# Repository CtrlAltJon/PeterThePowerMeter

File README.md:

# ⚡ Peter The Power Meter
### with ESP8266 and ADS1115

<p align="center">
  
</p>

## ⚠️ Disclaimer

> [!CAUTION]
> ### ⚠️ IMPORTANT SAFETY WARNING & DISCLAIMER
> **THIS PROJECT INVOLVES WORKING WITH HIGH VOLTAGE (230VAC). HIGH VOLTAGE CAN CAUSE SEVERE INJURY, ELECTROCUTION, OR DEATH. FIRE HAZARD IS ALSO PRESENT.**
>
> This project is provided "as is", for educational and hobbyist purposes only. By using any part of this project (including hardware designs, PCB layouts, and software), you acknowledge and agree to the following:
>
> * **Assumption of Risk:** You are solely responsible for your own safety and for any damage caused by the assembly, testing, or use of this device.
> * **No Liability:** The author(s) shall not be held liable for any direct or indirect damages, including but not limited to: hardware failure, data loss, property damage (fire, short circuits), personal injury, or death, resulting from the use or misuse of this project.
> * **Assembly & Modification:** Any errors in assembly, soldering (e.g., solder bridges), component selection, firmware modification or others actions are the sole responsibility of the user.
> * **No Warranty:** There is no guarantee regarding the accuracy of measurements, the stability of the software, or the safety of the hardware design for long-term use.
> * **Local Standards:** It is the user's responsibility to ensure that the device complies with local electrical codes and safety regulations.
>
> **IF YOU ARE NOT EXPERIENCED IN WORKING WITH MAINS VOLTAGE, DO NOT ATTEMPT TO BUILD THIS PROJECT.**

## 📜 Revision History
* **00:** First release (30/05/2026)
* **01:** Hardware optimizations and professional safety compliance updates (17/06/2026)
  * **Complete 2.5mm High-Voltage Isolation:** Optimized the High Voltage (HV) layout to strictly enforce a minimum 2.5mm track-to-track clearance across the entire mains section. This includes adding physical PCB isolation slots (milling) between R28, R29, F1, and J3 (pin 2), and shifting transformer TR1 along with adjacent resistors slightly upward to eliminate any tight spacings.
  * **Industrial-Grade Reinforced Insulation:** Preserved the robust **8.0mm isolation barrier** natively designed between the HV and Low Voltage (LV) domains. By combining this wide clearance with the new track-to-track optimizations, the board fully satisfies the strict **Reinforced Insulation** requirements of the **IEC/EN 62368-1** standard (aligning with household and industrial appliance safety regulations like IEC 60335-1 / IEC 60730-1), drastically setting this architecture apart from typical, uncertified DIY designs.
  * **Power Rail & Logic Level Optimization:** Removed 1 pin from connector J11 to eliminate the +5VDC routing to the lateral pcb, successfully migrating the CH340C USB-to-Serial subsystem entirely to a +3.3VDC power rail.
  * **Component Reconfiguration:** Rewired pin 4 (V3) of the CH340C directly to the +3.3VDC rail (mandatory for stable 3.3V operation) while retaining C9 in the layout to act as an active power supply decoupling filter instead of a standard bypass to GND.

## 💡 Design Rationale & Project Overview

### 1.1 System Architecture
This project is a Digital Power Meter designed for real-time energy monitoring with acoustic alarm when a threshold is exceeded. The system is engineered to fit within a standard 1-module DIN rail enclosure (roughly the size of a standard miniature circuit breaker), making it ideal for integration into domestic electrical panels.

*Note: At the moment, the 3D design/CAD file for the DIN enclosure is not available. Contributions regarding the design of a suitable enclosure are highly welcome and would be a valuable addition to this project.*

The system architecture is based on the ESP8266 (ESP-12F) microcontroller, leveraging its Wi-Fi capabilities for IoT integration and an ADS1115 to read voltage and current. For system health, an onboard TFPT1206L1002DV temperature sensor is included to monitor the internal thermal conditions of the enclosure.

For local interaction, the device features a 0.96" color LCD display that provides real-time data visualization and configuration menus. Users can navigate through multiple data pages and perform basic setup tasks using a multi-function physical button. Additionally, the system hosts a built-in Web Server, allowing for advanced remote configuration, firmware updates (OTA), and detailed system management via an intuitive Web UI.

The measurement stage utilizes two primary sensors:
* **Voltage Sensing:** Handled via a dedicated voltage transformer ZMPT107-1 (TR1) for galvanic isolation and safety.
* **Current Sensing:** Implemented using the SCT-013 split-core current transformer (clamp meter).

Both sensors provide a 1VAC sinusoidal output. These signals are conditioned via a voltage divider network and sampled by an ADS1115 16-bit ADC, which communicates with the MCU via the I2C protocol.

### 1.2 Hardware Features & User Interface

<p align="center">
  
</p>

To optimize GPIO usage, a PCF8574 I/O expander is employed for digital signal management and future use. The user interface consists of:
* **Buttons:** A multi-function navigation button (Short press: Page toggle | Long press: Confirm/Action) and a dedicated Pin-hole Hardware Reset button connected directly to Pin 1 (RST) of the ESP8266.
* **Acoustic Feedback:** An active piezoelectric buzzer triggers an audible alarm when a software-defined power threshold is exceeded.
* **Thermal Monitoring:** An onboard TFPT1206L1002DV temperature sensor (PTC thermistor) is integrated into the circuit. This component allows the system to monitor the internal temperature of the enclosure.
* **Display:** A 0.96" Color LCD for local monitoring and basic interaction.
* **Web Server:** A Web User Interface for remote monitoring and full system configuration.

### 1.3 Power Supply & Protection
The device supports 2 power input options and 1 input 230VAC for Voltage reading:

* **Terminal Block (J1):** Accepts a +5VDC regulated supply.

> [!CAUTION]
> **No reverse polarity protection:** This input currently lacks reverse polarity protection; correct orientation is mandatory.

<p align="center">
  
</p>

* **USB Connector (J2):** For secondary power or debugging.
    * *Communication & Debugging:* This interface utilizes a CH340C USB-to-Serial bridge and a UMH3NFHATN transistor pair to communicate with the ESP8266. This setup enables full debugging, serial communication, and firmware programming (automatic reset/bootloader entry).
    * *Safety Feature:* The board implements a dual Schottky diode protection circuit on the positive rails of both J1 and J2. This prevents back-feeding, though it is recommended to disconnect J1 when using USB power.
    * *Overcurrent Protection:* The +5VDC main rail is protected by a MF-NSMF050-2 PTC (Resettable Fuse) rated at 500mA.
* **AC Voltage Input (J3):** High-voltage input for the ZMPT107-1 transformer.
    * *Polarity Recommendation:* Although the transformer operates on AC, it is strictly recommended to respect the Phase (L) and Neutral (N) markings.
    <p align="center">
      
    </p>

    * *Safety Rationale:* The protection fuse is located exclusively on the Phase line. Inverting the polarity would mean that, in the event of a fault or a blown fuse, the Neutral line would be disconnected while the entire internal circuit remains energized (live) through the Phase line. This creates a severe electrocution hazard even when the device appears to be non-functional.
    * *Safety Design:* The circuit features a 250mA T (Slow-blow) fuse placed exclusively on the Phase line. Additionally, the line is equipped with three resistors in series designed to limit the current to 1mA RMS at 230V, providing an essential layer of protection for the sensing stage.

### 1.4 Operational Limits & Grid Compatibility
This device is specifically designed and calibrated for 230VAC/50Hz Phase-Neutral grids (Standard European Grid).

* **Voltage Specificity:** The internal components, including the protection resistors and the ZMPT107-1 transformer ratio, are optimized for 230V. Use with different mains voltages (e.g., 110-120V) may result in inaccurate readings or insufficient signal-to-noise ratio.
* **Frequency Specificity:** The system is tuned for 50Hz operation. While the magnetic components (TR1 and CT) can physically handle 60Hz, the firmware's sampling window and RMS calculation algorithms are optimized for a 20ms period.
* **Warning:** Operation on different grid standards, high-voltage industrial lines, or Phase-to-Phase configurations (without a neutral line) may exceed the safety ratings of the components and the fuse, leading to hardware failure or fire hazard.

## 🌐 2.0 Connectivity & Software Integration
The firmware architecture features a built-in Web Server for real-time monitoring, local configuration, and connections management (Wi-Fi and MQTT). The device natively supports the MQTT protocol for a smart home integration with platforms such as Home Assistant.

### 2.0.1 LCD User Interface (Vertical Orientation)
Navigation is handled via the multi-function button (Short press: Page toggle | Long press: Confirm/Action).

* **Page 1: Real-time Monitor**
    * Power: Current power consumption displayed in kW.
    * Temperature: PCB temperature in °C.
    * Graph: A rolling history graph showing power trends (approx. 1-minute window).
    * Status Badges: Dynamic icons for Wi-Fi connection status and MQTT connection status.
* **Page 2: Power Threshold Configuration**
    * Displays the active alarm threshold (Watts).
    * Allows cyclic adjustment of the new threshold (100W increments) via long-press.
* **Page 3: Voltage Monitoring**
    * Displays the real-time mains voltage (V).
* **Page 4: Acoustic Alarm Settings**
    * Displays and cycles through buzzer modes: Continuous, Slow Intermittent, or Fast Intermittent.
* **Page 5: Save Settings**
    * Summarizes settings. Action: A long-press commits settings to non-volatile memory.
* **Page 6: System Information**
    * Displays network details: Hostname, SSID, IP Address, and Firmware Version.
* **Page 7: System Tools**
    * AP Mode, Reboot device, and Reset (Factory Reset). Requires a long-press with a visual timer-bar.

### 2.0.2 Web Interface & Configuration
The device features a responsive Web UI. Users can connect via browser to the device's IP (visible on LCD page 6).

#### Home Page (Real-Time Dashboard)
* **Connectivity Status:** Dynamic badges for AP Mode, Wi-Fi, and MQTT.
* **Live Telemetry:** Power (W), Voltage (V), Current (A).
* **System Uptime:** Tracks operational time in "Days hh:mm:ss" format.
* **Data Refresh:** Auto-refresh every 10 seconds or manual button.

#### Configuration Page
* **General Settings:** Hostname, Manufacturer, Language (IT/EN), Alarm Threshold, Buzzer Mode.
* **Wi-Fi Setup:** Credentials and IP Assignment (DHCP or Static IP).
* **MQTT Setup (Optional):** Broker IP, Port, and Authentication.
* **Buttons:** Save & Reboot, Reboot, Firmware Update (OTA), Home.

## 🛠️ Manufacturing & Assembly Notes

### 3.0 Hardware Configuration
**ADS1115 I2C Address Selection:** Hardware-defined through two "0-Ohm bridge" resistors: R16 and R17. Only one of these resistors must be populated at a time:
* **R16:** Connects the ADDR pin to +3.3V, ADS1115 Address `0x49`
* **R17:** Connects the ADDR pin to GND, ADS1115 Address `0x48` (Default).

**Safety Design:** To prevent assembly errors, the PCB layout utilizes a shared common pad for both R16 and R17. This physical constraint makes it nearly impossible to populate both resistors simultaneously, effectively protecting the +3.3V rail from a direct short circuit to Ground. However, be careful when assembling.

## Assembly Layout: TOP Layer
<p align="center">
  
</p>

## Assembly Layout: BOTTOM Layer
<p align="center">
  
</p>

## Dimensions
<p align="center">
  
</p>

## 💻 4.0 Firmware
Peter The Power Meter has an embedded firmware designed for real-time single-phase energy monitoring. The system samples AC voltage and current waveforms, calculates Root Mean Square (RMS) values and active power consumption, provides a multi-page visual interface on a TFT display, and integrates with home automation systems via the MQTT protocol.

### Technical Specifications
* **Language:** C++ (Standard C++11/14).
* **Framework:** Arduino Core for ESP8266.
* **Development Environment:** PlatformIO.
* **Core Hardware:** Espressif ESP8266 (e.g., Wemos D1 Mini).
* **Data Acquisition:** External ADS1115 16-bit ADC connected via I2C for high-precision differential sampling.
* **Sensor Support:** Current Transformers (SCT-013), Voltage Transformers (ZMPT107-1), and PTC temperature sensors (TFPT1206).

### Key Features
* **High-Speed Sampling & RMS Calculation:** Performs rapid sampling of sinusoidal signals to calculate precise Voltage RMS, Current RMS, and Active Power (W) over a sliding 1-second window.
* **Display Management:** Features a multi-page User Interface on an ST7735 (0.96" TFT) display; includes real-time power trend graphs, connectivity status badges, and system information pages.
* **IoT & Home Automation:**
    * **MQTT Telemetry:** Transmits energy data using a time-weighted average calculated over the publishing interval (default 20s).
    * **Home Assistant Integration:** Fully supports Auto-Discovery, automatically creating sensors and configuration entities (Select/Number) within Home Assistant.
* **Embedded Web Server:** A built-in web portal protected by HTTP Basic Authentication allows users to configure WiFi credentials, MQTT settings, alarm thresholds, and perform fine sensor calibration (offset and scale).
* **Alarm System:** Manages a buzzer via a PCF8574 I/O expander with programmable modes (Continuous, Slow Pulse, Fast Pulse) triggered when power exceeds a user-defined threshold.
* **Reliability & Maintenance:**
    * **Resilient Connectivity:** Implements an exponential backoff strategy for WiFi and MQTT reconnection.
    * **OTA Updates:** Supports Over-The-Air firmware updates through the web interface.
    * **Localization:** Built-in multi-language support (English and Italian) using PROGMEM to optimize RAM usage.

### 4.0.1 Sensor Calibration & Physics Guide (include/config.h)
The following constants define how the raw electrical signals from the sensors are translated into human-readable values (Amps, Volts, Watts).

#### Current Conversion (FACTOR_A_V)
* **Description:** This is the scaling factor for the Current Transformer (CT). It converts the voltage measured by the ADC into RMS Amperes.
* **Formula:** `I_RMS = V_ADC * FACTOR_A_V`.
* **Configuration:** The `FACTOR_A_V` of 25.0f is set based on the characteristics of the SCT-013 current transformer.
* **When to change:**
    1. You replace the SCT-013 with a model that has a different Current/Voltage ratio (e.g., 30A/1V or 100A/50mA).
    2. You add or change an external burden resistor in parallel with the CT output.

#### Voltage Conversion (FACTOR_V_V)
* **Description:** This factor scales the low-voltage signal from the ZMPT107-1 transformer back to the actual grid voltage.
* **Formula:** `V_Grid = V_ADC * FACTOR_V_V`.
* **Configuration:** The `FACTOR_V_V` of 246.0f is derived directly from the ratio of the primary resistance (246KΩ) to the burden resistance (1KΩ).
* **When to change:** If you modify the scaling "divider" (e.g., changing series resistors on the Primary side or the burden resistor on the Secondary side).

#### ADC Precision & Sampling Rate
* **ADC Precision:** `ADS_GAIN` (GAIN_TWO) sets the full-scale range to ±2.048V, with an `ADS_MULTIPLIER` of 0.0000625.
* **Sampling Rate:** 860 Samples Per Second is the maximum stable rate for the ADS1115 and provides high fidelity for power calculations.

#### Noise, Safety, and Temperature
* **CURRENT_NOISE_FLOOR (0.002f):** A software filter that forces the current to 0.0A if the measured voltage is below 2mV.
* **VOLTAGE_MIN_THRESHOLD (50.0f):** If the measured voltage is below 50V, the system assumes the sensor is faulty and falls back to 230V.
* **Temperature Monitoring:** The firmware averages 10 readings (`PTC_AVG_SAMPLES`) to stabilize the PTC sensor data; if the temperature exceeds `TEMP_WARNING_THRESHOLD` (45.0°C), the display text turns RED.

| Constant | Default Value | Unit | Description |
| :--- | :--- | :--- | :--- |
| FACTOR_A_V | 25.0 | A/V | Ratio of Amps per Volt from the CT circuit. |
| FACTOR_V_V | 246.0 | V/V | Ratio of Grid Volts per Volt from the VT circuit. |
| ADS_GAIN | GAIN_TWO | - | Sets ADC input range to ±2.048V. |
| ADS_SPS | 860 | Hz | Samples taken per second from the AC wave. |
| CURRENT_NOISE_FLOOR | 0.002 | V | Minimum voltage to consider a valid current reading. |
| VOLTAGE_MIN_THRESHOLD | 50.0 | V | Voltage below which the system uses a fallback value. |

### 4.0.2 Per-device calibration limits (include/config.h)
These constants define the acceptable range and default values for the calibration parameters stored in EEPROM.

* **Scale Factors:** `CAL_SCALE_DEFAULT` is 1.0f (no correction), with a range between 0.1f and 10.0f.
* **Voltage Offset Limits:** -500.0f to 500.0f Volts.
* **Current Offset Limits:** -100.0f to 100.0f Amperes.
* **Temperature Offset Limits:** -50.0f to 50.0f degrees Celsius.

| Constant | Default/Range | Unit | Description |
| :--- | :--- | :--- | :--- |
| CAL_SCALE_DEFAULT | 1.0f | - | Default multiplicative scale factor. |
| CAL_SCALE_MIN | 0.1f | - | Minimum allowed value for scale factors. |
| CAL_SCALE_MAX | 10.0f | - | Maximum allowed value for scale factors. |
| CAL_OFFSET_V_MIN | -500.0f | V | Minimum allowed voltage offset. |
| CAL_OFFSET_V_MAX | 500.0f | V | Maximum allowed voltage offset. |
| CAL_OFFSET_A_MIN | -100.0f | A | Minimum allowed current offset. |
| CAL_OFFSET_A_MAX | 100.0f | A | Maximum allowed current offset. |
| CAL_OFFSET_TEMP_MIN | -50.0f | °C | Minimum allowed temperature offset. |
| CAL_OFFSET_TEMP_MAX | 50.0f | °C | Maximum allowed temperature offset. |

### 4.0.3 PTC Calibration & Hardware (include/config.h)
The device monitors internal temperature using the TFPT1206 series PTC sensor.

* **PTC_V_SOURCE:** 3.3f (Standard logic voltage).
* **PTC_R_PULLUP:** 33,000 Ω (Fixed resistor R7).
* **ADC Compensation:** Constants `PTC_R_DIVIDER_TOTAL` and `PTC_R_DIVIDER_LOAD` compensate for the voltage divider on the ESP8266 ADC input stage.
* **Sensor Characteristics:** `PTC_NOMINAL_RES` (10,000 Ω at 25°C) and `PTC_COEFF` (0.00411) define the resistance-to-temperature curve.

| Constant | Default Value | Unit | Description |
| :--- | :--- | :--- | :--- |
| PTC_V_SOURCE | 3.3 | V | Logic source voltage for the sensing branch. |
| PTC_R_PULLUP | 33,000 | Ω | Fixed pull-up resistor ($R_7$) in the divider. |
| PTC_NOMINAL_RES | 10,000 | Ω | PTC resistance at 25°C. |
| PTC_COEFF | 0.00411 | - | TCR (Temperature Coefficient) of the sensor. |
| PTC_R_DIVIDER_TOTAL | 100,220 | Ω | ADC input stage total resistance ($R_{21} + R_{22}$). |

## 🤝 Contributing

Contributions, issues, and feature requests are welcome!
Feel free to [open an issue](https://github.com/CtrlAltJon/PeterThePowerMeter/issues) or submit a pull request.

## 🔜 Coming Soon
I am currently in the process of refining and cleaning up the firmware comments to ensure the code is as clear and readable as possible, even though the project is fully functional.
I am also polishing the documentation and preparing additional guides that I'll upload to the repository soon.
Currently seeking help with:
* Enclosure Design: I'm looking for contributors to design a 3D-printable enclosure compatible with a standard 1-module DIN rail format. I think I'll be able to upload at least the STL file soon, but not the project.

## 📝 License

This project is licensed under the MIT License. See the [LICENSE](LICENSE) file for details.

## 👤 Author

CtrlAltJon

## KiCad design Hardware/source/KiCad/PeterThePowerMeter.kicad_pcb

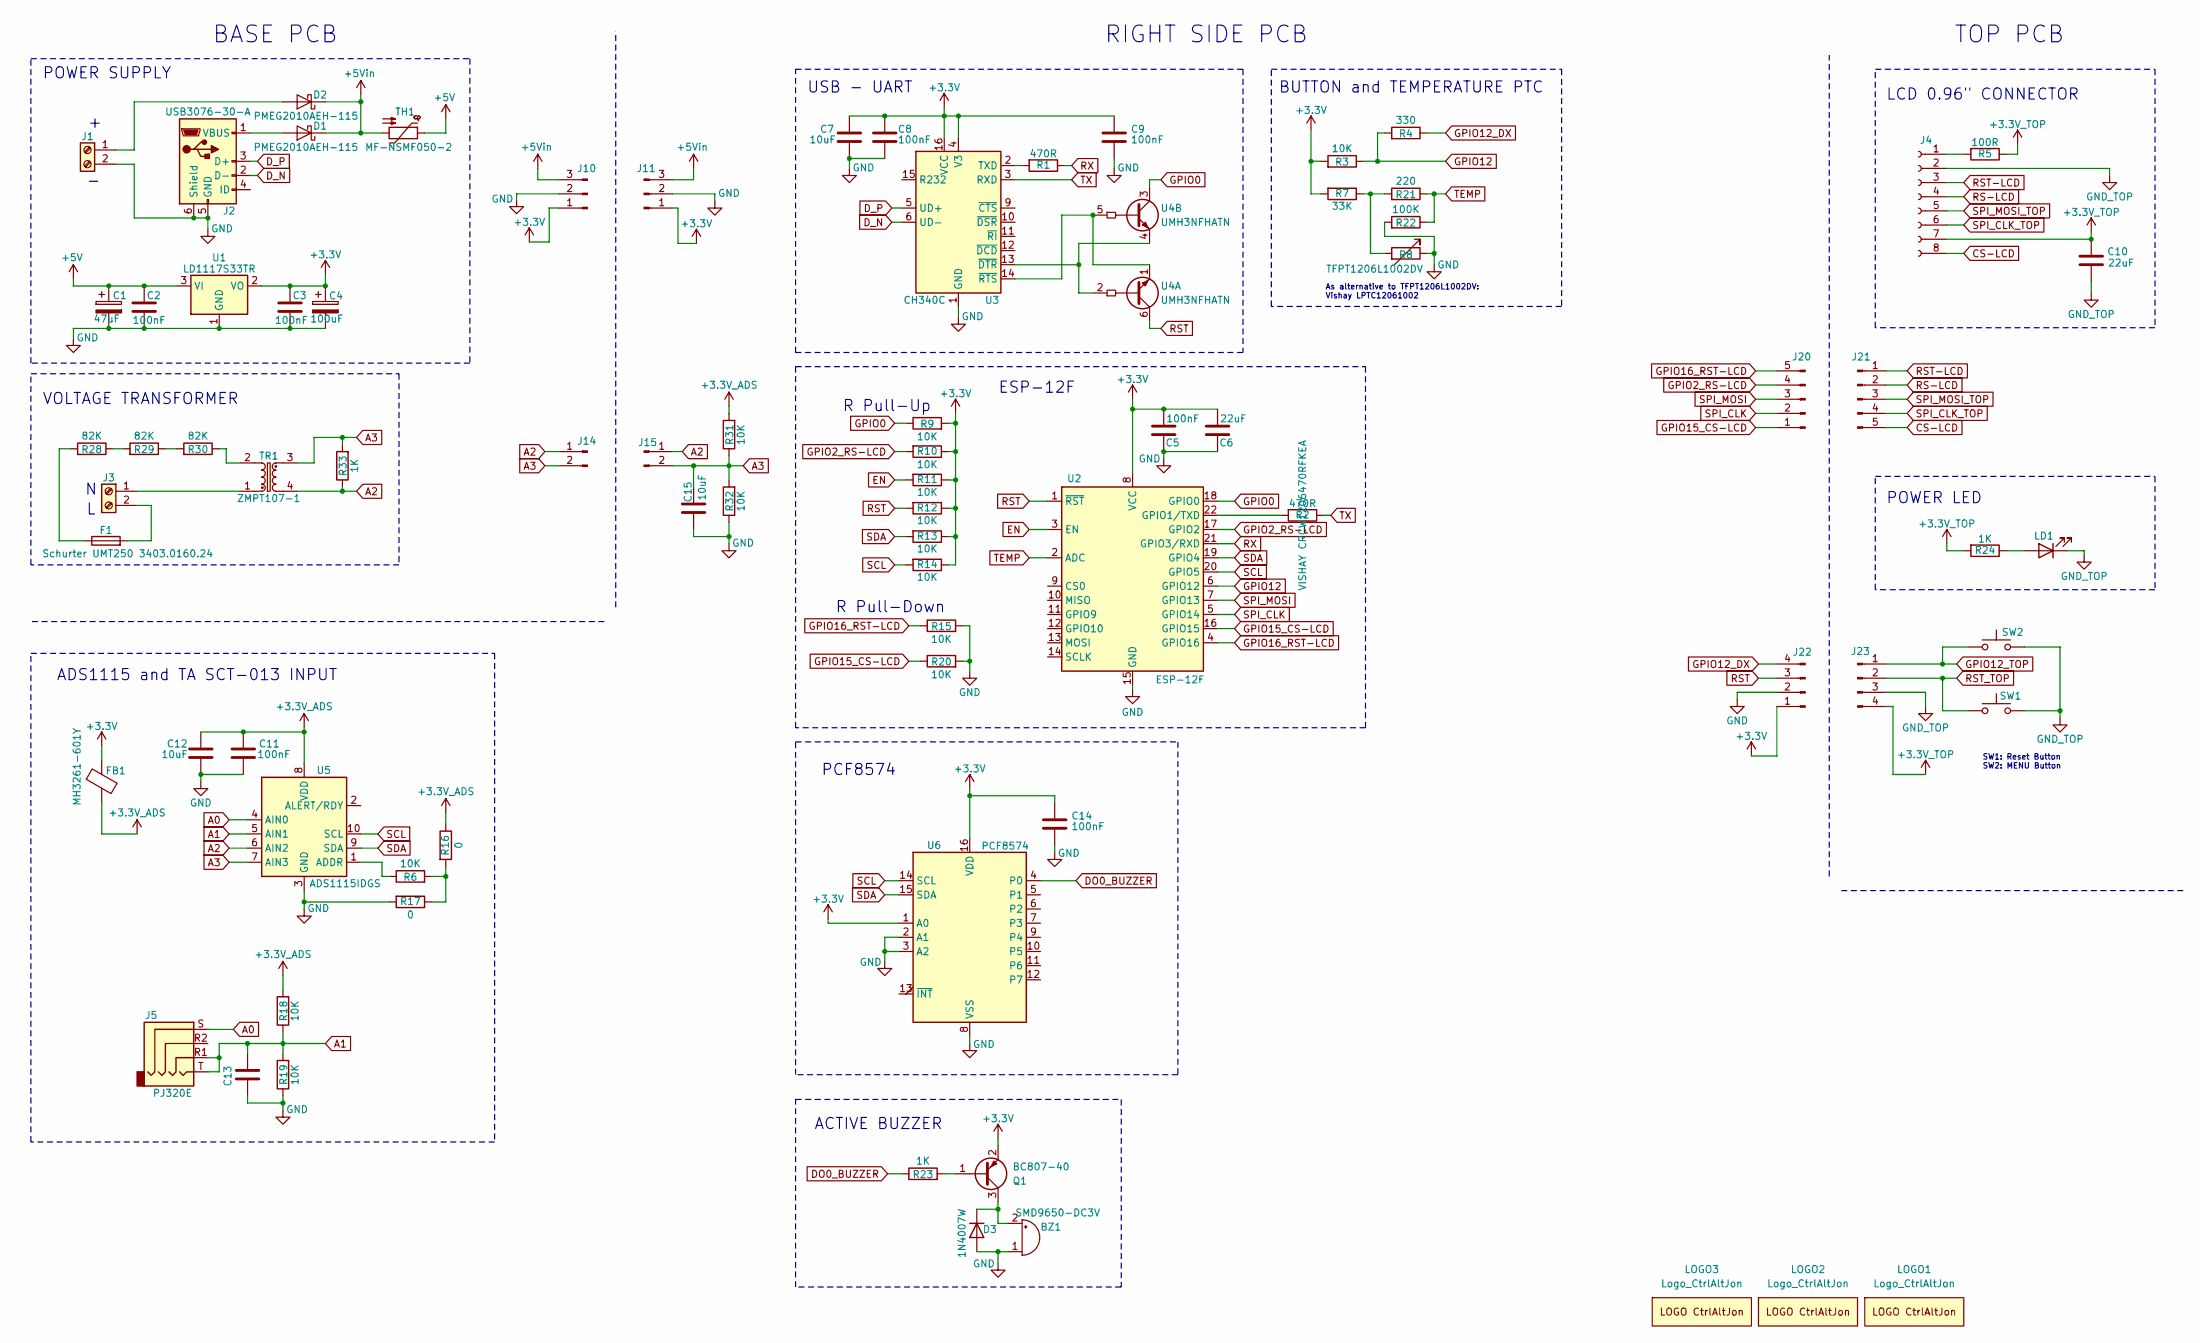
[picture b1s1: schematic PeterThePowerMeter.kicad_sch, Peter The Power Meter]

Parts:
BZ1: SMD9650-DC3V; Buzzer_CUI_CPT-9019S-SMT; LCSC C49246960
C1: 47uF; CP_Radial_D6.3mm_P2.50mm; LCSC C1580807
C2, C3, C5, C8, C9, C11, C14: 100nF; C_1206_3216Metric_Pad1.33x1.80mm_HandSolder; LCSC C2167356
C4: 100uF; CP_Radial_D6.3mm_P2.50mm; LCSC C1589590
C6, C10: 22uF; C_1206_3216Metric_Pad1.33x1.80mm_HandSolder; LCSC C318754
C7, C12, C13, C15: 10uF; C_1206_3216Metric_Pad1.33x1.80mm_HandSolder; LCSC C89632
D1, D2: PMEG2010AEH-115; D_SOD-123F; LCSC C110921
D3: 1N4007W; D_SOD-123; LCSC C3018540
F1: Schurter UMT250 3403.0160.24; Fuse_Schurter_UMZ250; LCSC C3163460
FB1: MH3261-601Y; L_1206_3216Metric; LCSC C840591
J1, J3: Screw_Terminal_01x02; PhoenixContact_MSTBA_2,5_2-G_1x02_P5.00mm_Horizontal; LCSC C90074
J2: USB3076-30-A; USB_Micro-B_GCT_USB3076-30-A; LCSC C6007475
J4: Conn_01x08_Socket; Hirose_FH12-8S-0.5SH_1x08-1MP_P0.50mm_Horizontal
J5: PJ320E; Jack_3.5mm_PJ320E_Horizontal; LCSC C2939183
J10: Conn_01x03_Pin; PinHeader_1x03_P2.54mm_Vertical
J11: Conn_01x03_Pin; PinHeader_1x03_P2.54mm_Horizontal
J14: Conn_01x02_Pin; PinHeader_1x02_P2.54mm_Vertical
J15: Conn_01x02_Pin; PinHeader_1x02_P2.54mm_Horizontal
J20: Conn_01x05_Pin; PinHeader_1x05_P2.54mm_Horizontal
J21: Conn_01x05_Pin; PinHeader_1x05_P2.54mm_Vertical
J22: Conn_01x04_Male; PinHeader_1x04_P2.54mm_Horizontal
J23: Conn_01x04_Male; PinHeader_1x04_P2.54mm_Vertical
LD1: LED; LED_1206_3216Metric; LCSC C133134
LOGO1, LOGO2, LOGO3: Logo_CtrlAltJon
Q1: BC807-40; SOT-23; LCSC C5184433
R1, R2: 470R; R_1206_3216Metric_Pad1.30x1.75mm_HandSolder; LCSC C844876
R3, R6, R9, R10, R11, R12, R13, R14, R15, R18, R19, R20, R31, R32: 10K; R_1206_3216Metric_Pad1.30x1.75mm_HandSolder; LCSC C132649
R4: 330; R_1206_3216Metric_Pad1.30x1.75mm_HandSolder; LCSC C114944
R5: 100R; R_1206_3216Metric_Pad1.30x1.75mm_HandSolder; LCSC C137392
R7: 33K; R_1206_3216Metric_Pad1.30x1.75mm_HandSolder; LCSC C7233588
R8: TFPT1206L1002DV; R_1206_3216Metric_Pad1.30x1.75mm_HandSolder; LCSC C2154230
R16, R17: 0; R_1206_3216Metric_Pad1.30x1.75mm_HandSolder; LCSC C137394
R21: 220; R_1206_3216Metric_Pad1.30x1.75mm_HandSolder; LCSC C137353
R22: 100K; R_1206_3216Metric_Pad1.30x1.75mm_HandSolder; LCSC C844863
R23, R24, R33: 1K; R_1206_3216Metric_Pad1.30x1.75mm_HandSolder; LCSC C131398
R28, R29, R30: 82K; R_1206_3216Metric_Pad1.30x1.75mm_HandSolder; LCSC C870906
SW1: 3.2x4.2; SW_Push_1P1T_NO_Vertical_Wuerth_434133025816; LCSC C470426
SW2: 434133025816; SW_Push_1P1T_NO_Vertical_Wuerth_434133025816; LCSC C470426
TH1: MF-NSMF050-2; R_1206_3216Metric_Pad1.30x1.75mm_HandSolder; LCSC C75464
TR1: ZMPT107-1; Transformer_Zeming_ZMPT107; LCSC C125191
U1: LD1117S33TR; SOT-223-3_TabPin2; LCSC C86781
U2: ESP-12F; ESP-12E; LCSC C82891
U3: CH340C; SOIC-16_3.9x9.9mm_P1.27mm; LCSC C84681
U4: UMH3NFHATN; SOT-363_SC-70-6; LCSC C3194552
U5: ADS1115IDGS; TSSOP-10_3x3mm_P0.5mm; LCSC C37593
U6: PCF8574; SOIC-16W_7.5x10.3mm_P1.27mm; LCSC C7605

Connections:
+3.3V: C3.1, C4.1, C5.1, C6.1, C7.1, C8.1, C9.1, C14.1, FB1.1, J10.1, J11.1, J22.1, Q1.2 (E), R3.2, R7.2, R9.2, R10.1, R11.1, R12.1, R13.1, R14.1, U1.2 (VO), U2.8 (VCC), U3.4 (V3), U3.16 (VCC), U6.1 (A0), U6.16 (VDD)
+3.3V_ADS: C11.2, C12.2, FB1.2, R16.1, R18.2, R31.2, U5.8 (VDD)
+3.3V_TOP: C10.1, J4.7, J23.4, R5.1, R24.2
+5V: C1.1, C2.1, TH1.1, U1.3 (VI)
+5Vin: D1.1 (K), D2.1 (K), J10.3, J11.3, TH1.2
A0: J5.S, U5.4 (AIN0)
A1: C13.2, J5.R1, J5.T, R18.1, R19.2, U5.5 (AIN1)
A2: J14.1, J15.1, R33.1, TR1.4, U5.6 (AIN2)
A3: C15.2, J14.2, J15.2, R31.1, R32.2, R33.2, TR1.3, U5.7 (AIN3)
CS-LCD: J4.8, J21.5
DO0_BUZZER: R23.1, U6.4 (P0)
D_N: J2.2 (D-), U3.6 (UD-)
D_P: J2.3 (D+), U3.5 (UD+)
EN: R11.2, U2.3 (EN)
GND: BZ1.1 (+), C1.2, C2.2, C3.2, C4.2, C5.2, C6.2, C7.2, C8.2, C9.2, C11.1, C12.1, C13.1, C14.2, C15.1, D3.2 (A), J1.2, J2.5 (GND), J2.6 (Shield), J10.2, J11.2, J22.2, R8.1, R15.2, R17.2, R19.1, R20.2, R22.2, R32.1, U1.1 (GND), U2.15 (GND), U3.1 (GND), U5.3 (GND), U6.2 (A1), U6.3 (A2), U6.8 (VSS)
GND_TOP: C10.2, J4.2, J23.3, LD1.1 (K), SW1.2, SW2.2
GPIO0: R9.1, U2.18 (GPIO0), U4.3 (C2)
GPIO2_RS-LCD: J20.4, R10.2, U2.17 (GPIO2)
GPIO12: R3.1, R4.2, U2.6 (GPIO12)
GPIO12_DX: J22.4, R4.1
GPIO12_TOP: J23.1, SW2.1
GPIO15_CS-LCD: J20.1, R20.1, U2.16 (GPIO15)
GPIO16_RST-LCD: J20.5, R15.1, U2.4 (GPIO16)
unnamed: BZ1.2 (-), D3.1 (K), Q1.3 (C)
unnamed: D1.2 (A), J2.1 (VBUS)
unnamed: D2.2 (A), J1.1
unnamed: F1.1, R28.2
unnamed: J3.1, TR1.1
unnamed: F1.2, J3.2
unnamed: J4.1, R5.2
unnamed: LD1.2 (A), R24.1
unnamed: Q1.1 (B), R23.2
unnamed: R6.2, R16.2, R17.1
unnamed: R7.1, R8.2, R21.2
unnamed: R28.1, R29.2
unnamed: R29.1, R30.2
unnamed: R30.1, TR1.2
unnamed: R2.2, U2.22 (GPIO1/TXD)
unnamed: R1.2, U3.2 (TXD)
unnamed: U3.13 (~DTR), U4.2 (B1), U4.4 (E2)
unnamed: U3.14 (~RTS), U4.1 (E1), U4.5 (B2)
unnamed: R6.1, U5.1 (ADDR)
RS-LCD: J4.4, J21.2
RST: J22.3, R12.2, U2.1 (~RST), U4.6 (C1)
RST-LCD: J4.3, J21.1
RST_TOP: J23.2, SW1.1
RX: R1.1, U2.21 (GPIO3/RXD)
SCL: R14.2, U2.20 (GPIO5), U5.10 (SCL), U6.14 (SCL)
SDA: R13.2, U2.19 (GPIO4), U5.9 (SDA), U6.15 (SDA)
SPI_CLK: J20.2, U2.5 (GPIO14)
SPI_CLK_TOP: J4.6, J21.4
SPI_MOSI: J20.3, U2.7 (GPIO13)
SPI_MOSI_TOP: J4.5, J21.3
TEMP: R21.1, R22.1, U2.2 (ADC)
TX: R2.1, U3.3 (RXD)

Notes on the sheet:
ADS1115 and TA SCT-013 INPUT
POWER LED
VOLTAGE TRANSFORMER
USB - UART
ESP-12F
R Pull-Up
PCF8574
BASE PCB
LCD 0.96" CONNECTOR
RIGHT SIDE PCB
R Pull-Down
POWER SUPPLY
ACTIVE BUZZER
As alternative to TFPT1206L1002DV: Vishay LPTC12061002
TOP PCB
SW1: Reset Button SW2: MENU Button
BUTTON and TEMPERATURE PTC

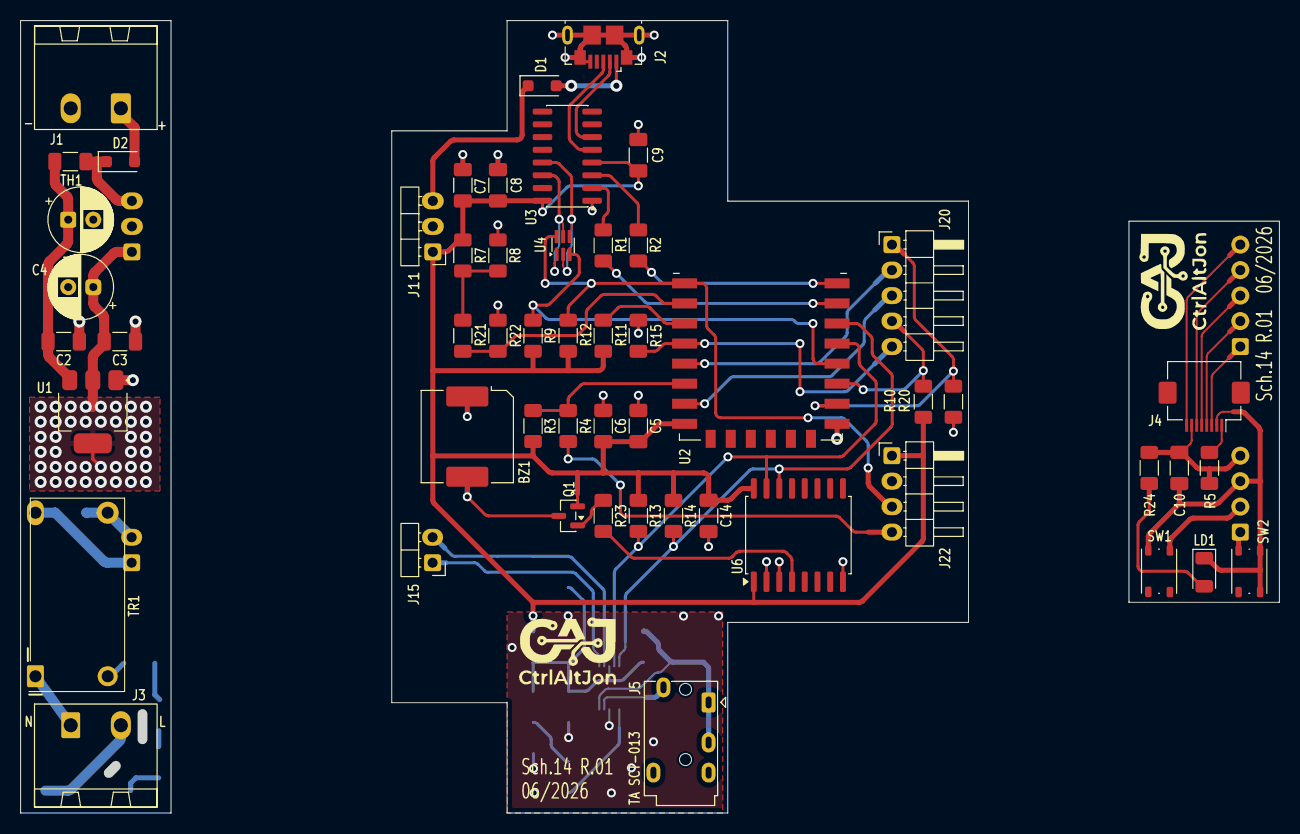
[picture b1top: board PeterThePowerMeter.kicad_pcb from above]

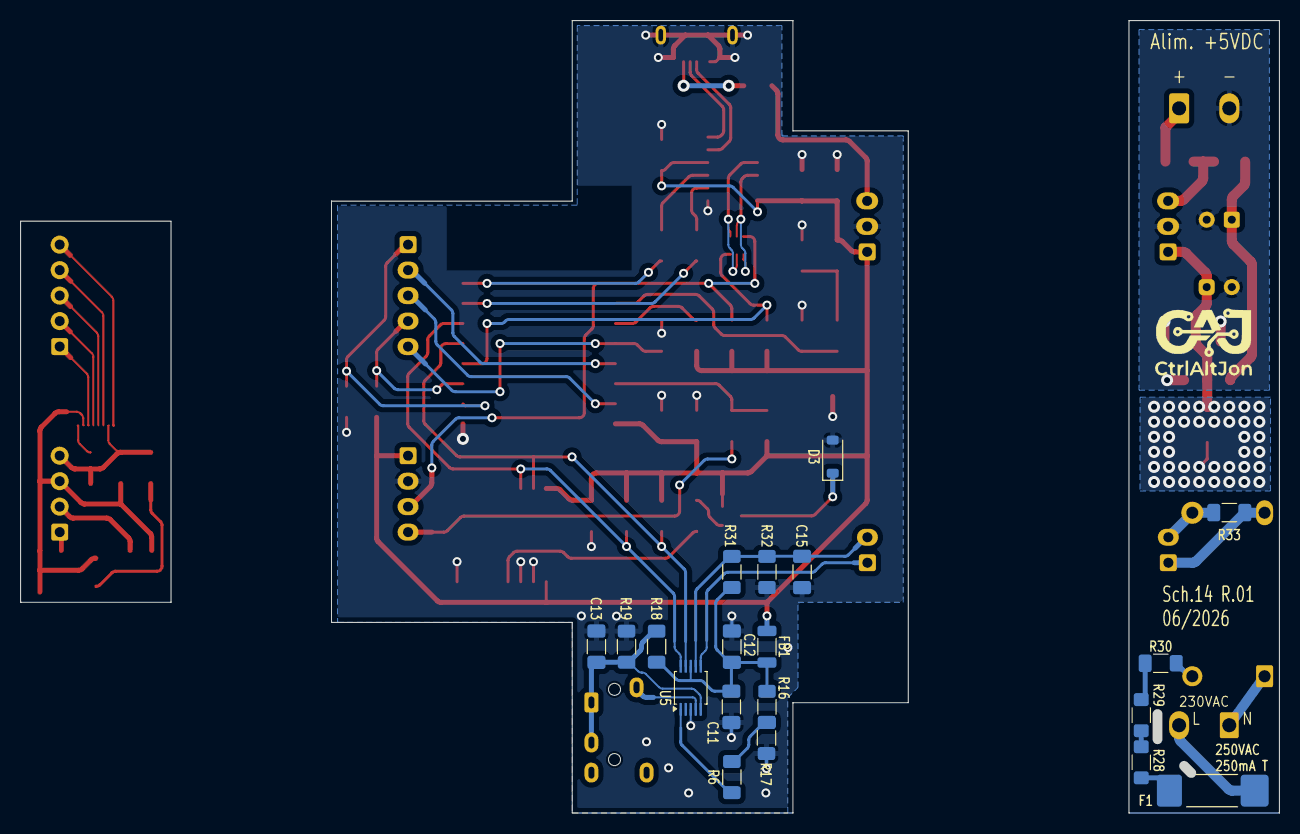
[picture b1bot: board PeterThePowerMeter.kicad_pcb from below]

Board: 2 copper layers, 125.5 x 79.0 mm, 79 parts (22 on the bottom side), 55 nets.

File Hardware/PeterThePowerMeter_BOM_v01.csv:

Comment,Designator,Footprint,LCSC,Quantity
0,"R16,R17",R_1206_3216Metric_Pad1.30x1.75mm_HandSolder,C137394,2
100K,R22,R_1206_3216Metric_Pad1.30x1.75mm_HandSolder,C844863,1
100R,R5,R_1206_3216Metric_Pad1.30x1.75mm_HandSolder,C137392,1
100nF,"C11,C14,C2,C3,C5,C8,C9",C_1206_3216Metric_Pad1.33x1.80mm_HandSolder,C2167356,7
100uF,C4,CP_Radial_D6.3mm_P2.50mm,C1589590,1
10K,"R10,R11,R12,R13,R14,R15,R18,R19,R20,R3,R31,R32,R6,R9",R_1206_3216Metric_Pad1.30x1.75mm_HandSolder,C132649,14
10uF,"C12,C13,C15,C7",C_1206_3216Metric_Pad1.33x1.80mm_HandSolder,C89632,4
1K,"R23,R24,R33",R_1206_3216Metric_Pad1.30x1.75mm_HandSolder,C131398,3
1N4007W,D3,D_SOD-123,C3018540,1
220,R21,R_1206_3216Metric_Pad1.30x1.75mm_HandSolder,C137353,1
22uF,"C10,C6",C_1206_3216Metric_Pad1.33x1.80mm_HandSolder,C318754,2
3.2x4.2,SW1,SW_Push_1P1T_NO_Vertical_Wuerth_434133025816,C470426,1
330,R4,R_1206_3216Metric_Pad1.30x1.75mm_HandSolder,C114944,1
33K,R7,R_1206_3216Metric_Pad1.30x1.75mm_HandSolder,C7233588,1
434133025816,SW2,SW_Push_1P1T_NO_Vertical_Wuerth_434133025816,C470426,1
470R,"R1,R2",R_1206_3216Metric_Pad1.30x1.75mm_HandSolder,C844876,2
47uF,C1,CP_Radial_D6.3mm_P2.50mm,C1580807,1
82K,"R28,R29,R30",R_1206_3216Metric_Pad1.30x1.75mm_HandSolder,C870906,3
ADS1115IDGS,U5,TSSOP-10_3x3mm_P0.5mm,C37593,1
BC807-40,Q1,SOT-23,C5184433,1
CH340C,U3,SOIC-16_3.9x9.9mm_P1.27mm,C84681,1
ESP-12F,U2,ESP-12E,C82891,1
LD1117S33TR,U1,SOT-223-3_TabPin2,C86781,1
LED,LD1,LED_1206_3216Metric,C133134,1
MF-NSMF050-2,TH1,R_1206_3216Metric_Pad1.30x1.75mm_HandSolder,C75464,1
MH3261-601Y,FB1,L_1206_3216Metric,C840591,1
PCF8574,U6,SOIC-16W_7.5x10.3mm_P1.27mm,C7605,1
PJ320E,J5,Jack_3.5mm_PJ320E_Horizontal,C2939183,1
PMEG2010AEH-115,"D1,D2",D_SOD-123F,C110921,2
SMD9650-DC3V,BZ1,Buzzer_CUI_CPT-9019S-SMT,C49246960,1
Schurter UMT250 3403.0160.24,F1,Fuse_Schurter_UMZ250,C3163460,1
Screw_Terminal_01x02,"J1,J3","PhoenixContact_MSTBA_2,5_2-G_1x02_P5.00mm_Horizontal",C90074,2
TFPT1206L1002DV,R8,R_1206_3216Metric_Pad1.30x1.75mm_HandSolder,C2154230,1
UMH3NFHATN,U4,SOT-363_SC-70-6,C3194552,1
USB3076-30-A,J2,USB_Micro-B_GCT_USB3076-30-A,C6007475,1
ZMPT107-1,TR1,Transformer_Zeming_ZMPT107,C125191,1

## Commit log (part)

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2026-04-19 Repo Creation
2026-04-19 Changed README.md
2026-04-19 Updated README.md with images
2026-04-21 Updated Images
2026-05-24 Upgrade documentation
2026-05-30 Upgrade many files for first upload
2026-05-30 Update Documentation
2026-05-30 Update Hardware files
2026-05-30 Upload some images, others soon
2026-05-31 Added LCD to BOM
2026-05-31 Updated documentation
2026-05-31 Uploaded demo video
2026-05-31 Uploaded hardware files and schematic
2026-05-31 Adding code of conduct
    Updated reporting method for unacceptable behavior.
2026-05-31 add issue templates
2026-05-31 Updated gitignore
2026-05-31 Uploaded CONTRIBUTING
2026-05-31 Uploaded PULL_REQUEST_TEMPLATE
2026-05-31 Uploaded SECURITY
2026-05-31 Updated docs & images
2026-05-31 Updated docs
2026-05-31 Updated BOM CH340G -> CH340C
2026-05-31 Updated doc guide
2026-05-31 Renamed Guide -> Manual
2026-06-17 Released 01 version

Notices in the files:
README.md:
📝 License:
This project is licensed under the MIT License. See the [LICENSE](LICENSE) file for details.
